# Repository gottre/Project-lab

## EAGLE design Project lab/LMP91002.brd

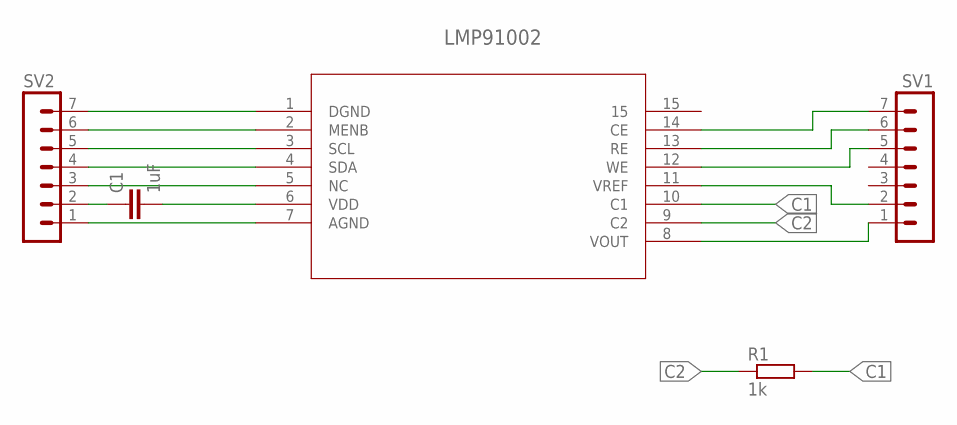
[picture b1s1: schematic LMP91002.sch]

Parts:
C1: 1uF; C0805
LMP91002: LMP91000_NHL_14; SDA14B
R1: 1k; M0805
SV1, SV2: MA07-1

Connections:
C1: LMP91002.10 (C1), R1.2
C2: LMP91002.9 (C2), R1.1
unnamed: LMP91002.7 (AGND), SV2.1
unnamed: LMP91002.14 (CE), SV1.7
unnamed: LMP91002.13 (RE), SV1.6
unnamed: LMP91002.1 (DGND), SV2.7
unnamed: LMP91002.12 (WE), SV1.5
unnamed: LMP91002.11 (VREF), SV1.2
unnamed: LMP91002.3 (SCL), SV2.5
unnamed: LMP91002.8 (VOUT), SV1.1
unnamed: LMP91002.2 (MENB), SV2.6
unnamed: LMP91002.4 (SDA), SV2.4
unnamed: LMP91002.5 (NC), SV2.3
unnamed: C1.1, SV2.2
unnamed: C1.2, LMP91002.6 (VDD)

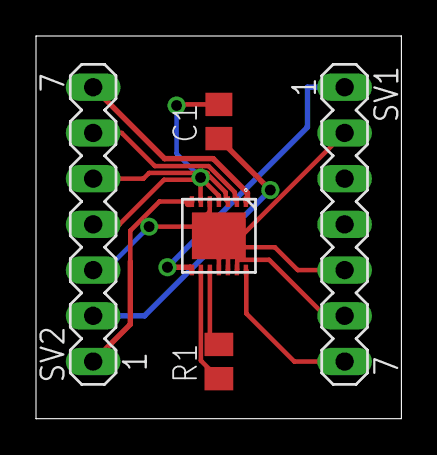
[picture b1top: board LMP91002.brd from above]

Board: 2 copper layers, 20.3 x 21.3 mm, 5 parts (0 on the bottom side), 15 nets.

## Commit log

2018-06-19 adding Project lab
